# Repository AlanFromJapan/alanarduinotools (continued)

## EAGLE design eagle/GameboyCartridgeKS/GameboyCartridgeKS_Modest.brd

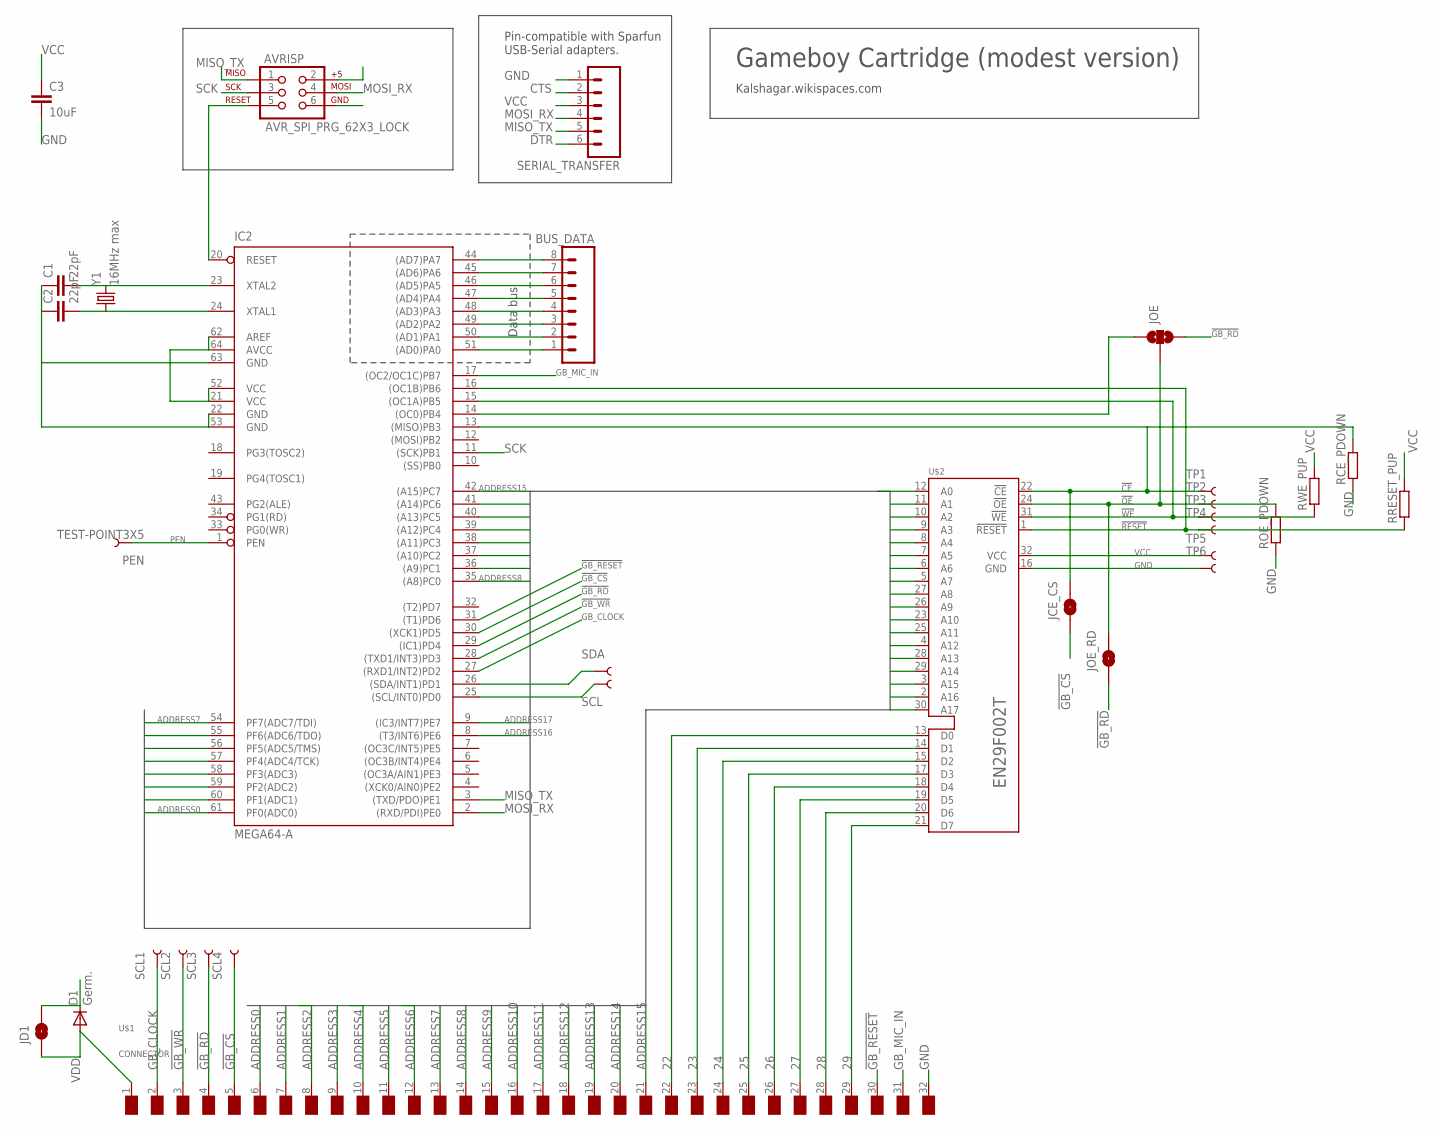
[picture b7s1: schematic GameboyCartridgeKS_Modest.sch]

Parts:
AVRISP: AVR_SPI_PRG_62X3_LOCK; 2X3_LOCK
BUS_DATA: M08NO_SILK; 1X08_PIN1_NO_SILK
C1, C2: 22pF; C0805K
C3: 10uF; C1206K
D1: Germ.; DO35-7
IC2: MEGA64-A; TQFP64
JCE_CS: JUMPER-PAD-2-NO; PAD-JUMPER-2-NO_NO_SILK
JD1: JUMPER-PAD-2-NO; PAD-JUMPER-2-NO_NO_SILK
JOE: JUMPER-PAD-3-NOYES_SILK; PAD-JUMPER-3-NO_YES_SILK
JOE_RD: JUMPER-PAD-2-NO; PAD-JUMPER-2-NO_NO_SILK
PEN: TEST-POINT3X5; PAD.03X.05
RCE_PDOWN: R-EU_R1206; R1206
ROE_PDOWN: R-EU_R1206; R1206
RRESET_PUP: R-EU_R1206; R1206
RWE_PUP: R-EU_R1206; R1206
SCL, SCL1, SCL2, SCL3, SCL4: TEST-POINT3X5; PAD.03X.05
SDA: TEST-POINT3X5; PAD.03X.05
SERIAL_TRANSFER: M06SILK_FEMALE_PTH; 1X06
TP1, TP2, TP3, TP4, TP5, TP6: TEST-POINT3X5; PAD.03X.05
U$1: CONNECTOR
U$2: EN29F002T; PLCC-S32
Y1: 16MHz max; HC49U-V

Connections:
22: BUS_DATA.1, IC2.51 ((AD0)PA0), U$1.22 (D0), U$2.13 (D0)
23: BUS_DATA.2, IC2.50 ((AD1)PA1), U$1.23 (D1), U$2.14 (D1)
24: BUS_DATA.3, IC2.49 ((AD2)PA2), U$1.24 (D2), U$2.15 (D2)
25: BUS_DATA.4, IC2.48 ((AD3)PA3), U$1.25 (D3), U$2.17 (D3)
26: BUS_DATA.5, IC2.47 ((AD4)PA4), U$1.26 (D4), U$2.18 (D4)
27: BUS_DATA.6, IC2.46 ((AD5)PA5), U$1.27 (D5), U$2.19 (D5)
28: BUS_DATA.7, IC2.45 ((AD6)PA6), U$1.28 (D6), U$2.20 (D6)
29: BUS_DATA.8, IC2.44 ((AD7)PA7), U$1.29 (D7), U$2.21 (D7)
!CE: IC2.13 ((MISO)PB3), JCE_CS.2, RCE_PDOWN.2, TP1.P$1, U$2.22 (!CE)
!GB_CS: IC2.30 ((XCK1)PD5), JCE_CS.1, SCL4.P$1, U$1.5 (/RCS)
!GB_RD: IC2.29 ((IC1)PD4), JOE.3, JOE_RD.1, SCL3.P$1, U$1.4 (/RD)
!GB_RESET: IC2.31 ((T1)PD6), U$1.30 (/RS)
!GB_WR: IC2.28 ((TXD1/INT3)PD3), SCL2.P$1, U$1.3 (/WR)
!OE: JOE.2, JOE_RD.2, ROE_PDOWN.2, TP2.P$1, U$2.24 (!OE)
!RESET: IC2.16 ((OC1B)PB6), RRESET_PUP.1, TP4.P$1, U$2.1 (!RESET)
!WE: IC2.15 ((OC1A)PB5), RWE_PUP.1, TP3.P$1, U$2.31 (!WE)
ADDRESS0: IC2.61 (PF0(ADC0)), U$1.6 (A0), U$2.12 (A0)
ADDRESS1: IC2.60 (PF1(ADC1)), U$1.7 (A1), U$2.11 (A1)
ADDRESS2: IC2.59 (PF2(ADC2)), U$1.8 (A2), U$2.10 (A2)
ADDRESS3: IC2.58 (PF3(ADC3)), U$1.9 (A3), U$2.9 (A3)
ADDRESS4: IC2.57 (PF4(ADC4/TCK)), U$1.10 (A4), U$2.8 (A4)
ADDRESS5: IC2.56 (PF5(ADC5/TMS)), U$1.11 (A5), U$2.7 (A5)
ADDRESS6: IC2.55 (PF6(ADC6/TDO)), U$1.12 (A6), U$2.6 (A6)
ADDRESS7: IC2.54 (PF7(ADC7/TDI)), U$1.13 (A7), U$2.5 (A7)
ADDRESS8: IC2.35 ((A8)PC0), U$1.14 (A8), U$2.27 (A8)
ADDRESS9: IC2.36 ((A9)PC1), U$1.15 (A9), U$2.26 (A9)
ADDRESS10: IC2.37 ((A10)PC2), U$1.16 (A10), U$2.23 (A10)
ADDRESS11: IC2.38 ((A11)PC3), U$1.17 (A11), U$2.25 (A11)
ADDRESS12: IC2.39 ((A12)PC4), U$1.18 (A12), U$2.4 (A12)
ADDRESS13: IC2.40 ((A13)PC5), U$1.19 (A13), U$2.28 (A13)
ADDRESS14: IC2.41 ((A14)PC6), U$1.20 (A14), U$2.29 (A14)
ADDRESS15: IC2.42 ((A15)PC7), U$1.21 (A15), U$2.3 (A15)
ADDRESS16: IC2.8 ((T3/INT6)PE6), U$2.2 (A16)
ADDRESS17: IC2.9 ((IC3/INT7)PE7), U$2.30 (A17)
CTS: SERIAL_TRANSFER.2
DTR: SERIAL_TRANSFER.6
GB_CLOCK: IC2.27 ((RXD1/INT2)PD2), SCL1.P$1, U$1.2 (NC)
GB_MIC_IN: IC2.17 ((OC2/OC1C)PB7), U$1.31 (VIN)
GND: AVRISP.6, C1.1, C2.1, C3.2, IC2.22 (GND), IC2.53 (GND), IC2.63 (GND), RCE_PDOWN.1, ROE_PDOWN.1, SERIAL_TRANSFER.1, TP6.P$1, U$1.32 (GND), U$2.16 (GND); also elsewhere on the board
MISO_TX: AVRISP.1, IC2.3 ((TXD/PDO)PE1), SERIAL_TRANSFER.5
MOSI_RX: AVRISP.4, IC2.2 ((RXD/PDI)PE0), SERIAL_TRANSFER.4
unnamed: C1.2, IC2.23 (XTAL2), Y1.2
unnamed: AVRISP.5, IC2.20 (RESET)
unnamed: C2.2, IC2.24 (XTAL1), Y1.1
unnamed: IC2.14 ((OC0)PB4), JOE.1
PEN: IC2.1 (PEN), PEN.P$1
SCK: AVRISP.3, IC2.11 ((SCK)PB1)
SCL: IC2.25 ((SCL/INT0)PD0), SCL.P$1
SDA: IC2.26 ((SDA/INT1)PD1), SDA.P$1
VCC: AVRISP.2, C3.1, D1.C, IC2.21 (VCC), IC2.52 (VCC), IC2.62 (AREF), IC2.64 (AVCC), JD1.2, RRESET_PUP.2, RWE_PUP.2, SERIAL_TRANSFER.3, TP5.P$1, U$2.32 (VCC); also elsewhere on the board
VDD: D1.A, JD1.1, U$1.1 (VDD)

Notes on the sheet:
Pin-compatible with Sparfun USB-Serial adapters.
Data bus
Kalshagar.wikispaces.com
Gameboy Cartridge (modest version)

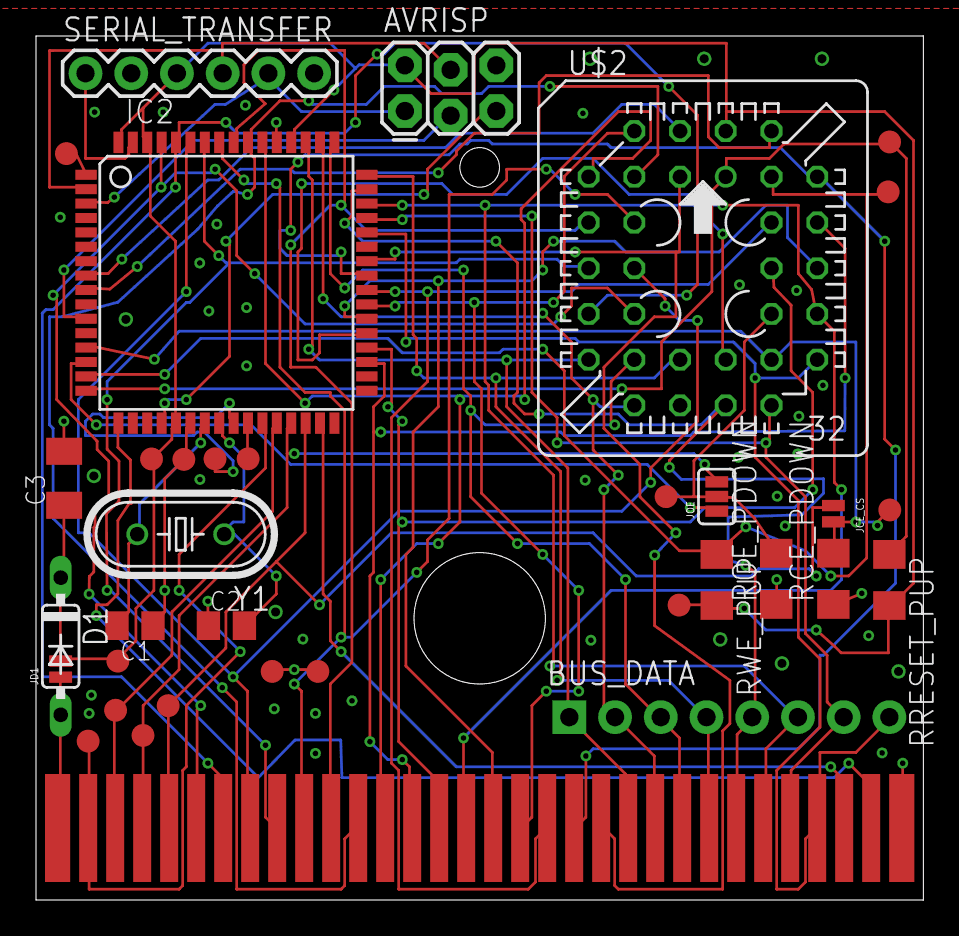
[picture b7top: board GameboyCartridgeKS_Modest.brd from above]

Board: 4 copper layers, 49.3 x 48.0 mm, 36 parts (0 on the bottom side), 49 nets.

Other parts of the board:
PEN1, PEN2, PEN3, PEN4: TEST-POINT3X5; PAD.03X.05
U$3: GAMEBOY_LOGO

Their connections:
GND: PEN1.P$1, PEN2.P$1; also elsewhere on the board
VCC: PEN3.P$1, PEN4.P$1; also elsewhere on the board

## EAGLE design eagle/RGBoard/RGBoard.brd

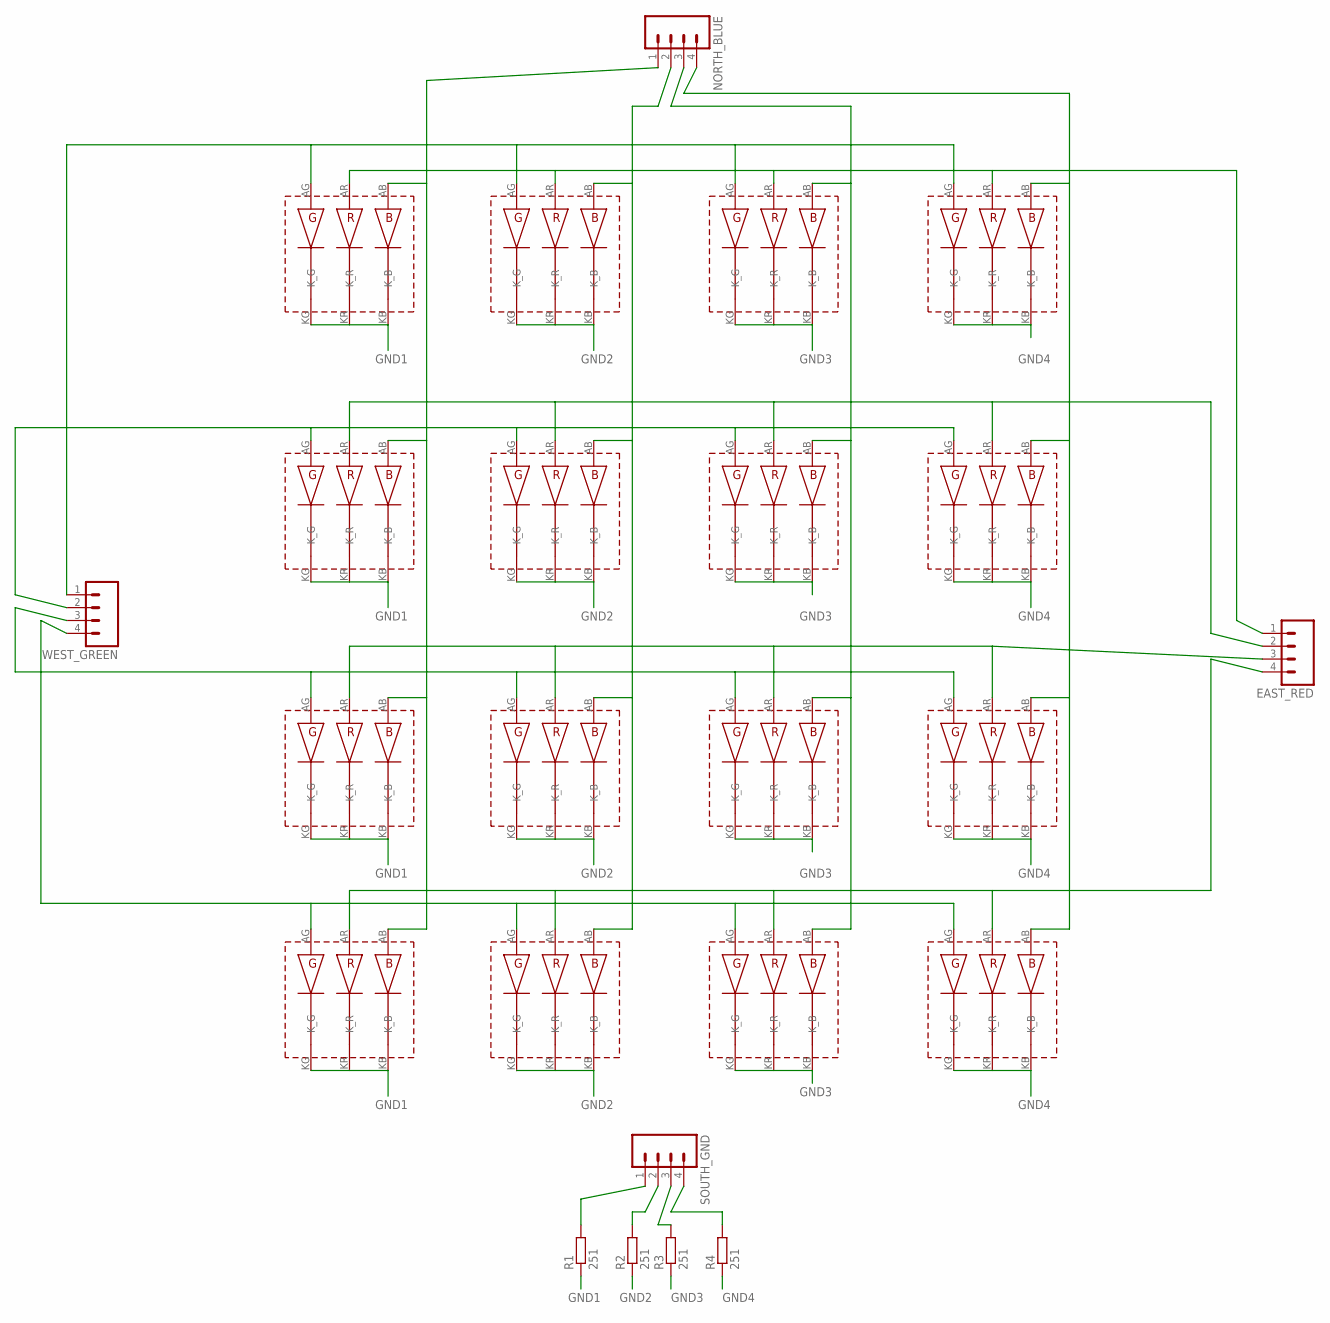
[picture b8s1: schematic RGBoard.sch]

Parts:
A1, A2, A3, A4: RGB-SMT-SQUARE; SMT-SQUARE6
B1, B2, B3, B4: RGB-SMT-SQUARE; SMT-SQUARE6
C1, C2, C3, C4: RGB-SMT-SQUARE; SMT-SQUARE6
D1, D2, D3, D4: RGB-SMT-SQUARE; SMT-SQUARE6
EAST_RED: M04PTH; 1X04
NORTH_BLUE: M04PTH; 1X04
R1, R2, R3, R4: 251; 0204/7
SOUTH_GND: M04PTH; 1X04
WEST_GREEN: M04PTH; 1X04

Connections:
GND1: A1.KB (K_B), A1.KG (K_G), A1.KR (K_R), B1.KB (K_B), B1.KG (K_G), B1.KR (K_R), C1.KB (K_B), C1.KG (K_G), C1.KR (K_R), D1.KB (K_B), D1.KG (K_G), D1.KR (K_R), R1.1
GND2: A2.KB (K_B), A2.KG (K_G), A2.KR (K_R), B2.KB (K_B), B2.KG (K_G), B2.KR (K_R), C2.KB (K_B), C2.KG (K_G), C2.KR (K_R), D2.KB (K_B), D2.KG (K_G), D2.KR (K_R), R2.1
GND3: A3.KB (K_B), A3.KG (K_G), A3.KR (K_R), B3.KB (K_B), B3.KG (K_G), B3.KR (K_R), C3.KB (K_B), C3.KG (K_G), C3.KR (K_R), D3.KB (K_B), D3.KG (K_G), D3.KR (K_R), R3.1
GND4: A4.KB (K_B), A4.KG (K_G), A4.KR (K_R), B4.KB (K_B), B4.KG (K_G), B4.KR (K_R), C4.KB (K_B), C4.KG (K_G), C4.KR (K_R), D4.KB (K_B), D4.KG (K_G), D4.KR (K_R), R4.1
unnamed: R1.2, SOUTH_GND.1
unnamed: R2.2, SOUTH_GND.2
unnamed: R3.2, SOUTH_GND.3
unnamed: R4.2, SOUTH_GND.4
unnamed: A1.AR (ANODE_R), A2.AR (ANODE_R), A3.AR (ANODE_R), A4.AR (ANODE_R), EAST_RED.1
unnamed: B1.AR (ANODE_R), B2.AR (ANODE_R), B3.AR (ANODE_R), B4.AR (ANODE_R), EAST_RED.2
unnamed: C1.AR (ANODE_R), C2.AR (ANODE_R), C3.AR (ANODE_R), C4.AR (ANODE_R), EAST_RED.3
unnamed: D1.AR (ANODE_R), D2.AR (ANODE_R), D3.AR (ANODE_R), D4.AR (ANODE_R), EAST_RED.4
unnamed: A1.AB (ANODE_B), B1.AB (ANODE_B), C1.AB (ANODE_B), D1.AB (ANODE_B), NORTH_BLUE.1
unnamed: A2.AB (ANODE_B), B2.AB (ANODE_B), C2.AB (ANODE_B), D2.AB (ANODE_B), NORTH_BLUE.2
unnamed: A3.AB (ANODE_B), B3.AB (ANODE_B), C3.AB (ANODE_B), D3.AB (ANODE_B), NORTH_BLUE.3
unnamed: A4.AB (ANODE_B), B4.AB (ANODE_B), C4.AB (ANODE_B), D4.AB (ANODE_B), NORTH_BLUE.4
unnamed: A1.AG (ANODE_G), A2.AG (ANODE_G), A3.AG (ANODE_G), A4.AG (ANODE_G), WEST_GREEN.1
unnamed: B1.AG (ANODE_G), B2.AG (ANODE_G), B3.AG (ANODE_G), B4.AG (ANODE_G), WEST_GREEN.2
unnamed: C1.AG (ANODE_G), C2.AG (ANODE_G), C3.AG (ANODE_G), C4.AG (ANODE_G), WEST_GREEN.3
unnamed: D1.AG (ANODE_G), D2.AG (ANODE_G), D3.AG (ANODE_G), D4.AG (ANODE_G), WEST_GREEN.4

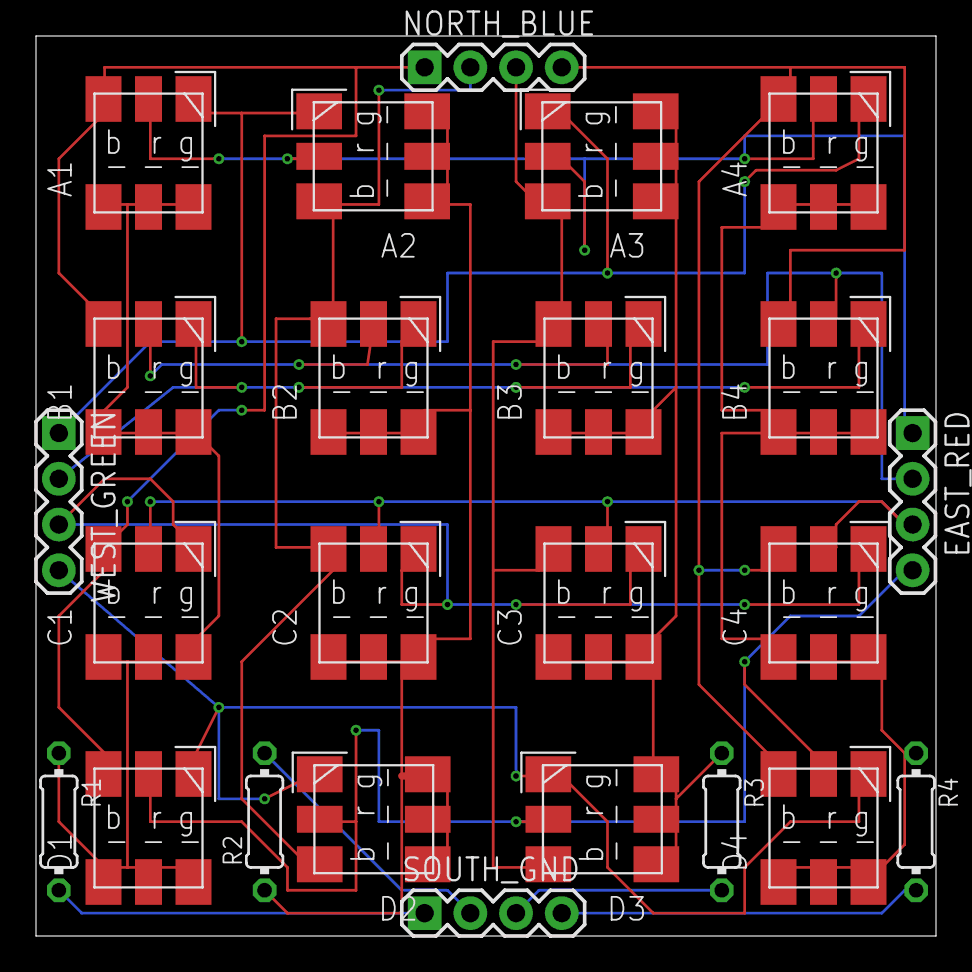
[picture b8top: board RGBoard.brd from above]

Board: 2 copper layers, 50.0 x 50.0 mm, 24 parts (0 on the bottom side), 20 nets.
